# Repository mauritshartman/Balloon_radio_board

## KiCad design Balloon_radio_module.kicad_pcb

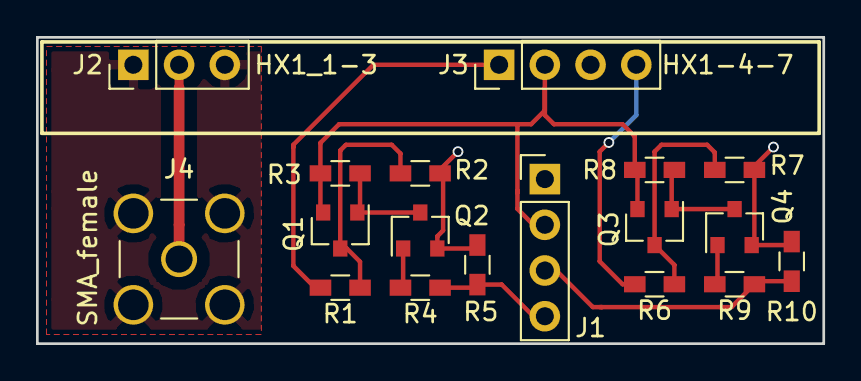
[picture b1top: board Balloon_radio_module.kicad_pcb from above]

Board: 2 copper layers, 43.7 x 17.0 mm, 18 parts (0 on the bottom side), 14 nets.

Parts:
J1: Conn_01x04; Pin_Header_Straight_1x04_Pitch2.54mm
J2: HX1_1-3; Pin_Header_Straight_1x03_Pitch2.54mm
J3: HX1-4-7; Pin_Header_Straight_1x04_Pitch2.54mm
J4: SMA_female; SMA_THT_Jack_Straight
Q1, Q3: MMBT3906; SOT-23
Q2, Q4: MMBT3904; SOT-23
R1, R6: 470; R_0603_HandSoldering
R2, R7: 10k; R_0603_HandSoldering
R3, R4, R5, R8, R9, R10: 100k; R_0603_HandSoldering

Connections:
+5V: J1.2, J3.2, Q1.2, Q3.2, R3.2, R8.2
/3.3v_EN: J1.4, R4.1, R5.2
/3.3v_TXD: J1.3, R9.1, R10.2
/5v_EN: J3.1, R1.2
/5v_TXD: J3.4, R6.2
GNDA: J2.1, J2.3, J4.2
GNDD: J1.1, J3.3, Q2.2, Q4.2, R2.1, R5.1, R7.1, R10.1
unnamed: J2.2, J4.1
unnamed: Q1.1, Q2.3, R3.1
unnamed: Q1.3, R1.1, R2.2
unnamed: Q2.1, R4.2
unnamed: Q3.1, Q4.3, R8.1
unnamed: Q3.3, R6.1, R7.2
unnamed: Q4.1, R9.2

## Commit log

2018-02-24 PCB layout done, SMA to be checked
2018-03-16 Final release
